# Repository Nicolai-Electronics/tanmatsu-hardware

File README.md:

# Tanmatsu

This repository contains the hardware design files for Tanmatsu, the terminal for hackers.

## Documentation

Need the schematic? [It's in this repository as a PDF file](schematic.pdf).

## License

This hardware design may be used under the terms of the [CERN-OHL-P](LICENSE) license.

All organization names, logos, trademarks and artwork including but not limited to the Nicolai Electronics and Tanmatsu branding are all rights reserved for their respective owners and may not be reproduced on derrivative works.

## Authors

Electronics design by:
 - [Nicolai Electronics](https://nicolaielectronics.nl)
 - [Paul Honig](https://github.com/ranzbak)

Special thanks to:
 - [Jay Visschedijk](https://github.com/JayVisschedijk) (Ergonomic board outline)
 - [Wietse Boonstra](https://github.com/Wietsman) (Component footprints)
 - [Kliment Yanev](https://github.com/kliment) (Review)
 - [Jelle Haandrikman](https://github.com/jhaand) (Review)

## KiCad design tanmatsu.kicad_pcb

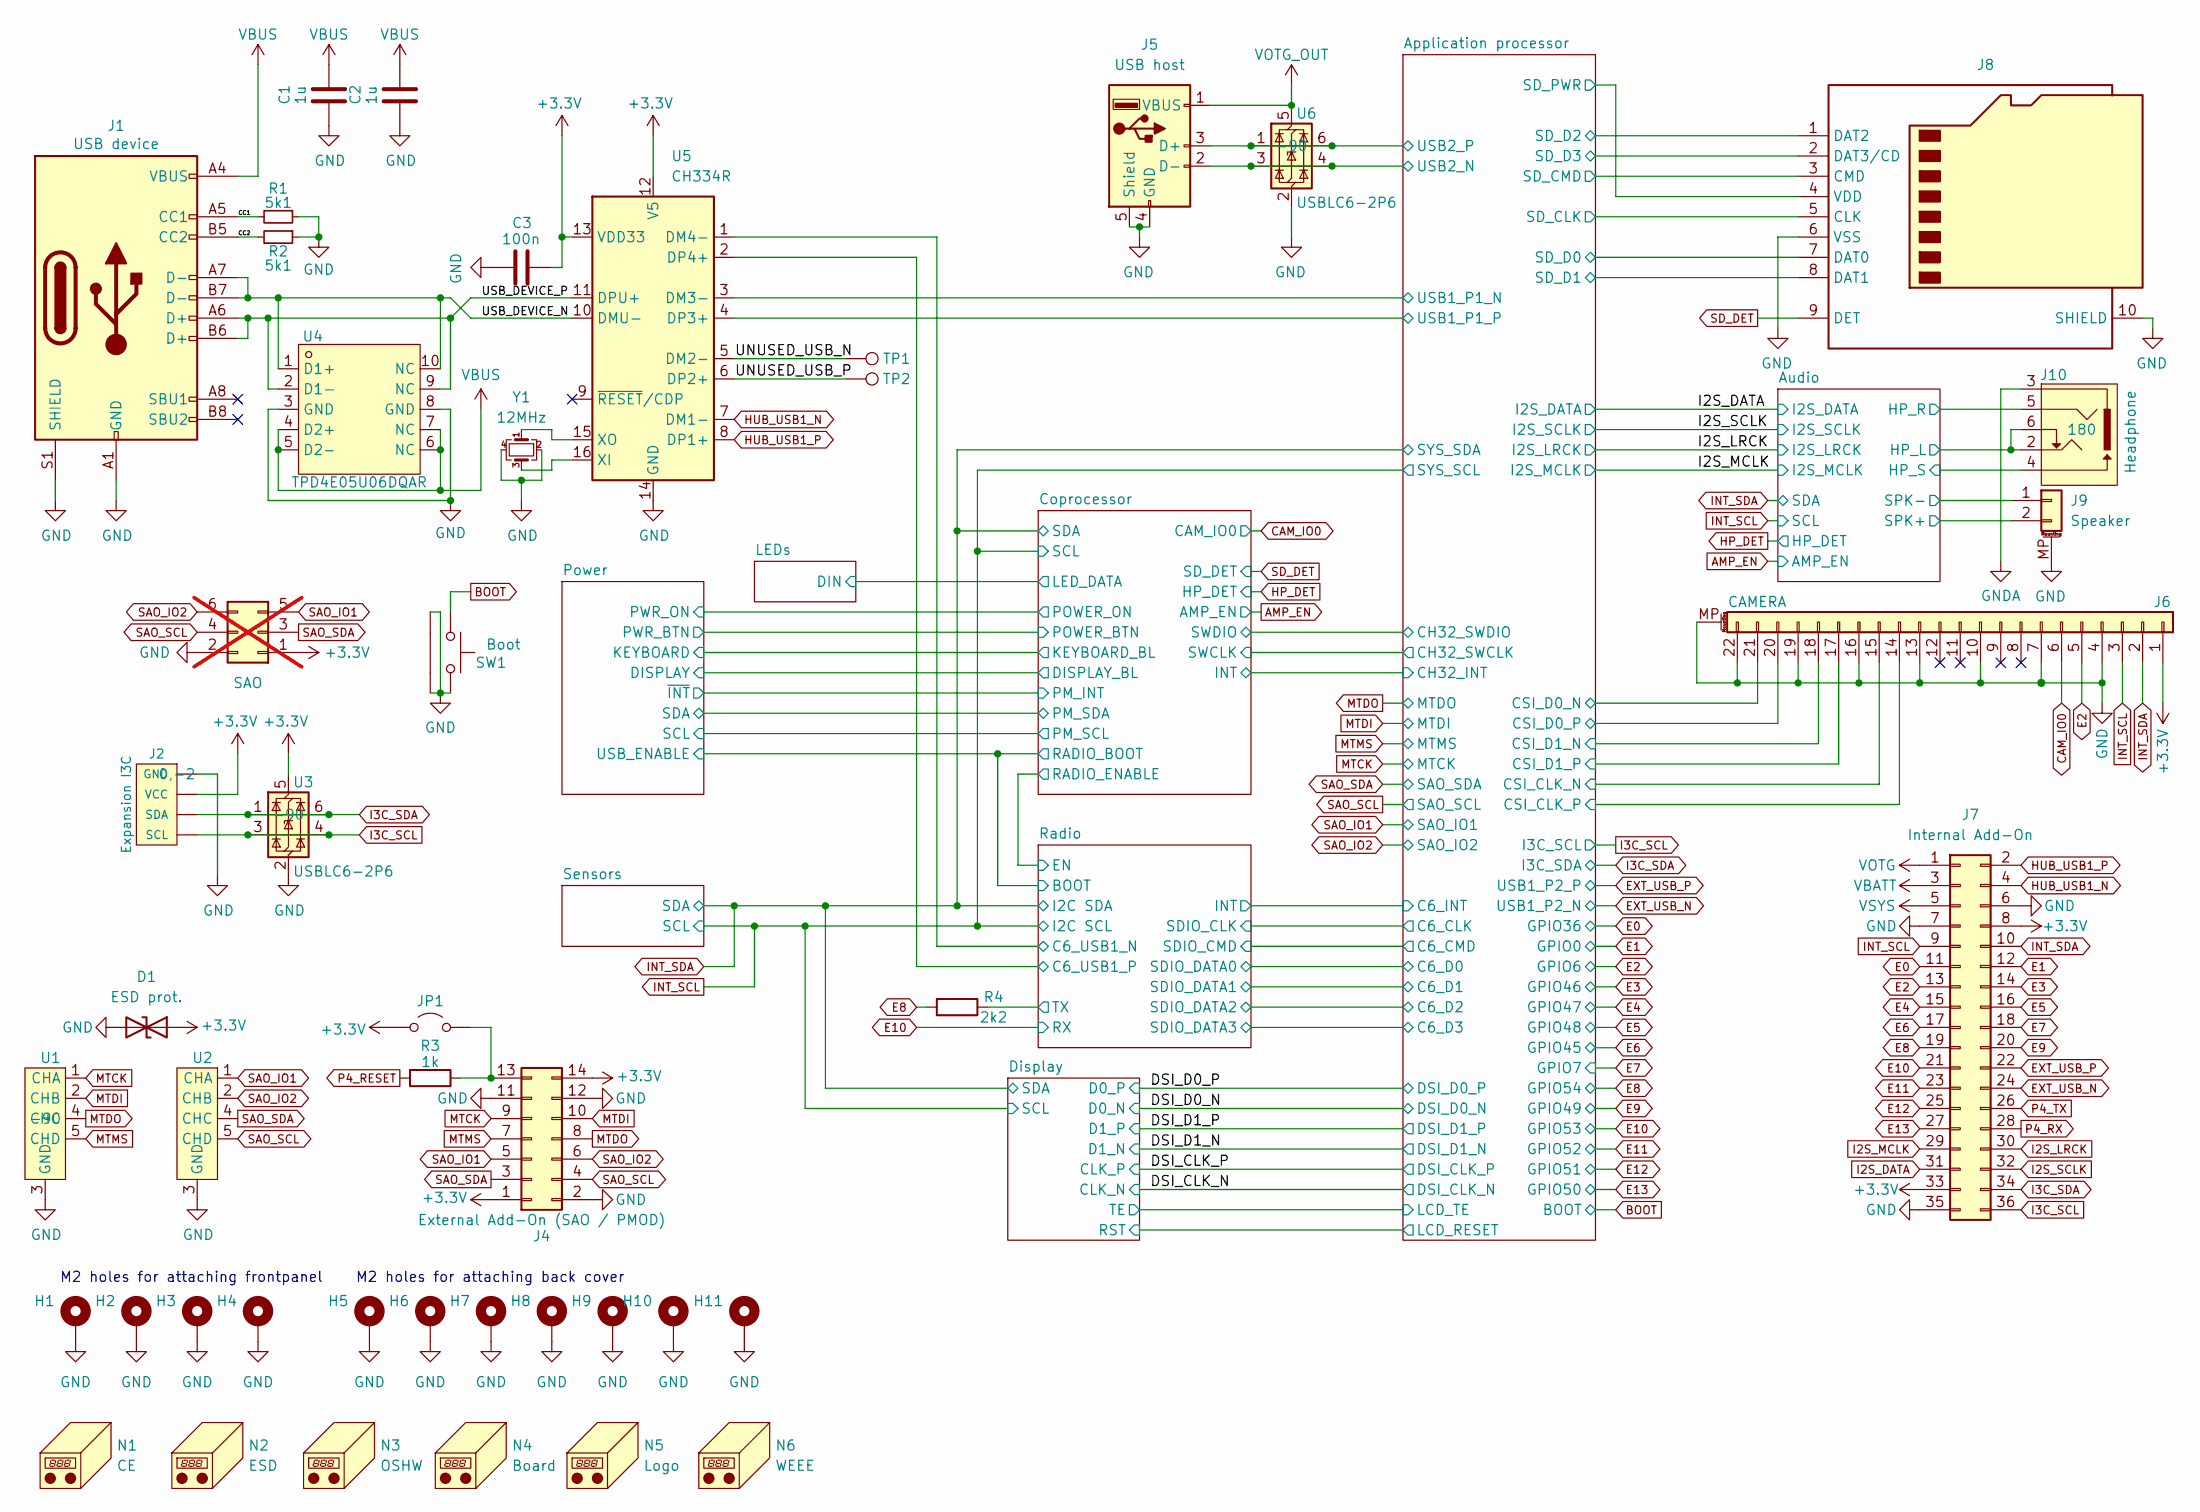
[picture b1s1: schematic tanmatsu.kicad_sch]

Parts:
C1, C2: 1u; C_0603_1608Metric; LCSC C5199872
C3: 100n; C_0402_1005Metric; LCSC C307331
D1: ESD prot.; D_SOD-323; LCSC C22363742
H1, H2, H3, H4, H5, H6, H7, H8, H9, H10, H11: Mounting hole; SMTSO2030CTJ; LCSC C2915626
J1: USB device; USB_C_Receptacle_HRO_TYPE-C-31-M-12; LCSC C165948
J2: Expansion I3C; 1X04_1MM_RA_GND; LCSC C7433425
J3: SAO; PinSocket_2x03_P2.54mm_Vertical_SMD; not fitted
J4: External Add-On (SAO / PMOD); PinSocket_2x07_P2.54mm_Horizontal; LCSC C2936004
J5: USB host; USB-A-TH_JTJ-USB-A-F-10.0-010; LCSC C42576
J6: CAMERA; FPC-SMD_XUNPU_FPC-0.5FX-22PWBH20; LCSC C3446014
J7: Internal Add-On; PinSocket_2x18_P2.54mm_Vertical_SMD; LCSC C3975163
J8: Micro_SD_Card; SD_Card-micro_socket_A; LCSC C7529389
J9: Speaker; Molex_PicoBlade_53261-0271_1x02-1MP_P1.25mm_Horizontal; LCSC C3029359
J10: Headphone; PJ-327ST-SMT; LCSC C319103
JP1: SolderJumper-2_P1.3mm_Open_RoundedPad1.0x1.5mm
N1: CE; CE-Logo_8.5x6mm_SilkScreen
N2: ESD; ESD-Logo_6.6x6mm_SilkScreen
N3: OSHW; OSHW-Logo2_14.6x12mm_SilkScreen
N4: Board; board
N5: Logo; logo_nicolai
N6: WEEE; WEEE-Logo_4.2x6mm_SilkScreen
R1, R2: 5k1; R_0402_1005Metric; LCSC C25905
R3: 1k; R_0402_1005Metric; LCSC C11702
R4: 2k2; R_0402_1005Metric; LCSC C25879
SW1: Boot; KEY-TH_TC-1101V-C-A-W; LCSC C318992
TP1: D-; TestPoint_Pad_D1.0mm
TP2: D+; TestPoint_Pad_D1.0mm
U1, U2: ESD; Diodes_UDFN-10_1.0x2.5mm_P0.5mm; LCSC C5180236
U3, U6: USBLC6-2P6; SOT-666; LCSC C2827693
U4: TPD4E05U06DQAR; USON-10_L2.5-W1.0-P0.50-BL; LCSC C138714
U5: CH334R; QSOP-16_3.9x4.9mm_P0.635mm; LCSC C4154405
Y1: 12MHz; Crystal_SMD_2520-4Pin_2.5x2.0mm; LCSC C284156

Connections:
+3.3V: C3.1, D1.1 (A1), J2.2 (VCC), J3.1, J4.1, J4.14, J6.1, J7.8, J7.33, JP1.1 (A), U3.5 (VBUS), U5.12 (V5), U5.13 (VDD33); also elsewhere on the board
/Application processor/CSI_CLK_N: J6.15; also elsewhere on the board
/Application processor/CSI_CLK_P: J6.14; also elsewhere on the board
/Application processor/CSI_D0_N: J6.21; also elsewhere on the board
/Application processor/CSI_D0_P: J6.20; also elsewhere on the board
/Application processor/CSI_D1_N: J6.18; also elsewhere on the board
/Application processor/CSI_D1_P: J6.17; also elsewhere on the board
/Application processor/SD_CLK: J8.5 (CLK); also elsewhere on the board
/Application processor/SD_CMD: J8.3 (CMD); also elsewhere on the board
/Application processor/SD_D0: J8.7 (DAT0); also elsewhere on the board
/Application processor/SD_D1: J8.8 (DAT1); also elsewhere on the board
/Application processor/SD_D2: J8.1 (DAT2); also elsewhere on the board
/Application processor/SD_D3: J8.2 (DAT3/CD); also elsewhere on the board
/Application processor/SD_PWR: J8.4 (VDD); also elsewhere on the board
/Application processor/USB1_P1_N: U5.3 (DM3-); also elsewhere on the board
/Application processor/USB1_P1_P: U5.4 (DP3+); also elsewhere on the board
/Application processor/USB2_N: J5.2 (D-), U6.3 (I/O2), U6.4 (I/O2); also elsewhere on the board
/Application processor/USB2_P: J5.3 (D+), U6.1 (I/O1), U6.6 (I/O1); also elsewhere on the board
/Audio/HP_L: J10.2, J10.6; also elsewhere on the board
/Audio/HP_R: J10.5; also elsewhere on the board
/Audio/HP_S: J10.4; also elsewhere on the board
/Audio/SPK+: J9.2; also elsewhere on the board
/Audio/SPK-: J9.1; also elsewhere on the board
/CC1: J1.A5 (CC1), R1.2
/CC2: J1.B5 (CC2), R2.2
/Radio/C6_USB1_N: U5.1 (DM4-); also elsewhere on the board
/Radio/C6_USB1_P: U5.2 (DP4+); also elsewhere on the board
/Radio/TX: R4.1; also elsewhere on the board
/UNUSED_USB_N: TP1.1 (1_1), U5.5 (DM2-)
/UNUSED_USB_P: TP2.1 (1_1), U5.6 (DP2+)
/USB_DEVICE_N: J1.A7 (D-), J1.B7 (D-), U4.1 (D1+), U4.10 (NC), U5.10 (DMU-)
/USB_DEVICE_P: J1.A6 (D+), J1.B6 (D+), U4.2 (D1-), U4.9 (NC), U5.11 (DPU+)
BOOT: SW1.1; also elsewhere on the board
CAM_IO0: J6.6; also elsewhere on the board
E0: J7.11; also elsewhere on the board
E1: J7.12; also elsewhere on the board
E2: J6.5, J7.13; also elsewhere on the board
E3: J7.14; also elsewhere on the board
E4: J7.15; also elsewhere on the board
E5: J7.16; also elsewhere on the board
E6: J7.17; also elsewhere on the board
E7: J7.18; also elsewhere on the board
E8: J7.19, R4.2; also elsewhere on the board
E9: J7.20; also elsewhere on the board
E10: J7.21; also elsewhere on the board
E11: J7.23; also elsewhere on the board
E12: J7.25; also elsewhere on the board
E13: J7.27; also elsewhere on the board
EXT_USB_N: J7.24; also elsewhere on the board
EXT_USB_P: J7.22; also elsewhere on the board
GND: C1.2, C2.2, C3.2, D1.2 (A2), H1.1 (1_1), H2.1 (1_1), H3.1 (1_1), H4.1 (1_1), H5.1 (1_1), H6.1 (1_1), H7.1 (1_1), H8.1 (1_1), H9.1 (1_1), H10.1 (1_1), H11.1 (1_1), J1.A1 (GND), J1.A12 (GND), J1.B1 (GND), J1.B12 (GND), J1.S1 (SHIELD), J2.1 (GND), J2.5, J2.6, J3.2, J4.2, J4.11, J4.12, J5.4 (GND), J5.5 (Shield), J6.4, J6.7, J6.10, J6.13, J6.16, J6.19, J6.22, J6.MP (MountPin), J7.6, J7.7, J7.35, J8.6 (VSS), J8.10 (SHIELD), J9.MP (MountPin), R1.1, R2.1, SW1.2, SW1.3, SW1.4, U1.3 (GND), U1.8 (GND), U2.3 (GND), U2.8 (GND), U3.2 (GND), U4.3 (GND), U4.8 (GND), U5.14 (GND), U6.2 (GND), Y1.2, Y1.4; also elsewhere on the board
GNDA: J10.3; also elsewhere on the board
HUB_USB1_N: J7.4, U5.7 (DM1-)
HUB_USB1_P: J7.2, U5.8 (DP1+)
I2S_DATA: J7.31; also elsewhere on the board
I2S_LRCK: J7.30; also elsewhere on the board
I2S_MCLK: J7.29; also elsewhere on the board
I2S_SCLK: J7.32; also elsewhere on the board
I3C_SCL: J2.4 (SCL), J7.36, U3.3 (I/O2), U3.4 (I/O2); also elsewhere on the board
I3C_SDA: J2.3 (SDA), J7.34, U3.1 (I/O1), U3.6 (I/O1); also elsewhere on the board
INT_SCL: J6.3, J7.9; also elsewhere on the board
INT_SDA: J6.2, J7.10; also elsewhere on the board
MTCK: J4.9, U1.1 (CHA), U1.10 (CHA); also elsewhere on the board
MTDI: J4.10, U1.2 (CHB), U1.9 (CHB); also elsewhere on the board
MTDO: J4.8, U1.4 (CHC), U1.7 (CHC); also elsewhere on the board
MTMS: J4.7, U1.5 (CHD), U1.6 (CHD); also elsewhere on the board
unnamed: J4.13, JP1.2 (B), R3.1
unnamed: U5.16 (XI), Y1.3
unnamed: U5.15 (XO), Y1.1
P4_RESET: R3.2; also elsewhere on the board
P4_RX: J7.28; also elsewhere on the board
P4_TX: J7.26; also elsewhere on the board
SAO_IO1: J3.5, J4.5, U2.1 (CHA), U2.10 (CHA); also elsewhere on the board
SAO_IO2: J3.6, J4.6, U2.2 (CHB), U2.9 (CHB); also elsewhere on the board
SAO_SCL: J3.4, J4.4, U2.5 (CHD), U2.6 (CHD); also elsewhere on the board
SAO_SDA: J3.3, J4.3, U2.4 (CHC), U2.7 (CHC); also elsewhere on the board
SD_DET: J8.9 (DET); also elsewhere on the board
VBATT: J7.3; also elsewhere on the board
VBUS: C1.1, C2.1, J1.A4 (VBUS), J1.A9 (VBUS), J1.B4 (VBUS), J1.B9 (VBUS), U4.4 (D2+), U4.5 (D2-), U4.6 (NC), U4.7 (NC); also elsewhere on the board
VOTG: J7.1; also elsewhere on the board
VOTG_OUT: J5.1 (VBUS), U6.5 (VBUS); also elsewhere on the board
VSYS: J7.5; also elsewhere on the board

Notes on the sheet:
M2 holes for attaching back cover
M2 holes for attaching frontpanel

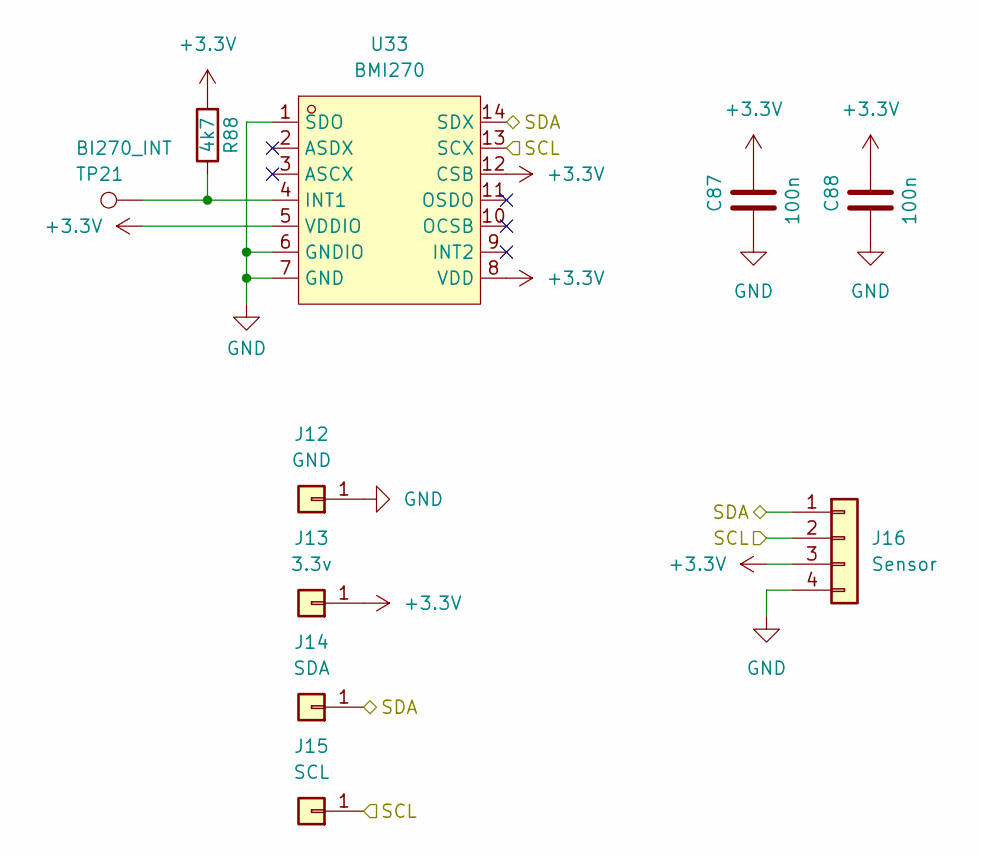
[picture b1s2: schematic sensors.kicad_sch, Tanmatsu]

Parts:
C87, C88: 100n; C_0402_1005Metric; LCSC C307331
J12: GND; Harwin S7091-42R
J13: 3.3v; Harwin S7091-42R
J14: SDA; Harwin S7091-42R
J15: SCL; Harwin S7091-42R
J16: Sensor; PinHeader_1x04_P2.54mm_Vertical; LCSC C2691448
R88: 4k7; R_0402_1005Metric; LCSC C25900
TP21: BI270_INT; TestPoint_Pad_D1.0mm
U33: BMI270; LGA-14_L3.0-W2.5-P0.50-BR; LCSC C2836813

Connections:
+3.3V: C87.1, C88.1, J13.1 (Pin_1_1), J16.3, R88.2, U33.5 (VDDIO), U33.8 (VDD), U33.12 (CSB); also elsewhere on the board
GND: C87.2, C88.2, J12.1 (Pin_1_1), J16.4, U33.1 (SDO), U33.6 (GNDIO), U33.7 (GND); also elsewhere on the board
INT_SCL: J15.1 (Pin_1_1), J16.2, U33.13 (SCX); also elsewhere on the board
INT_SDA: J14.1 (Pin_1_1), J16.1, U33.14 (SDX); also elsewhere on the board
unnamed: R88.1, TP21.1 (1_1), U33.4 (INT1)

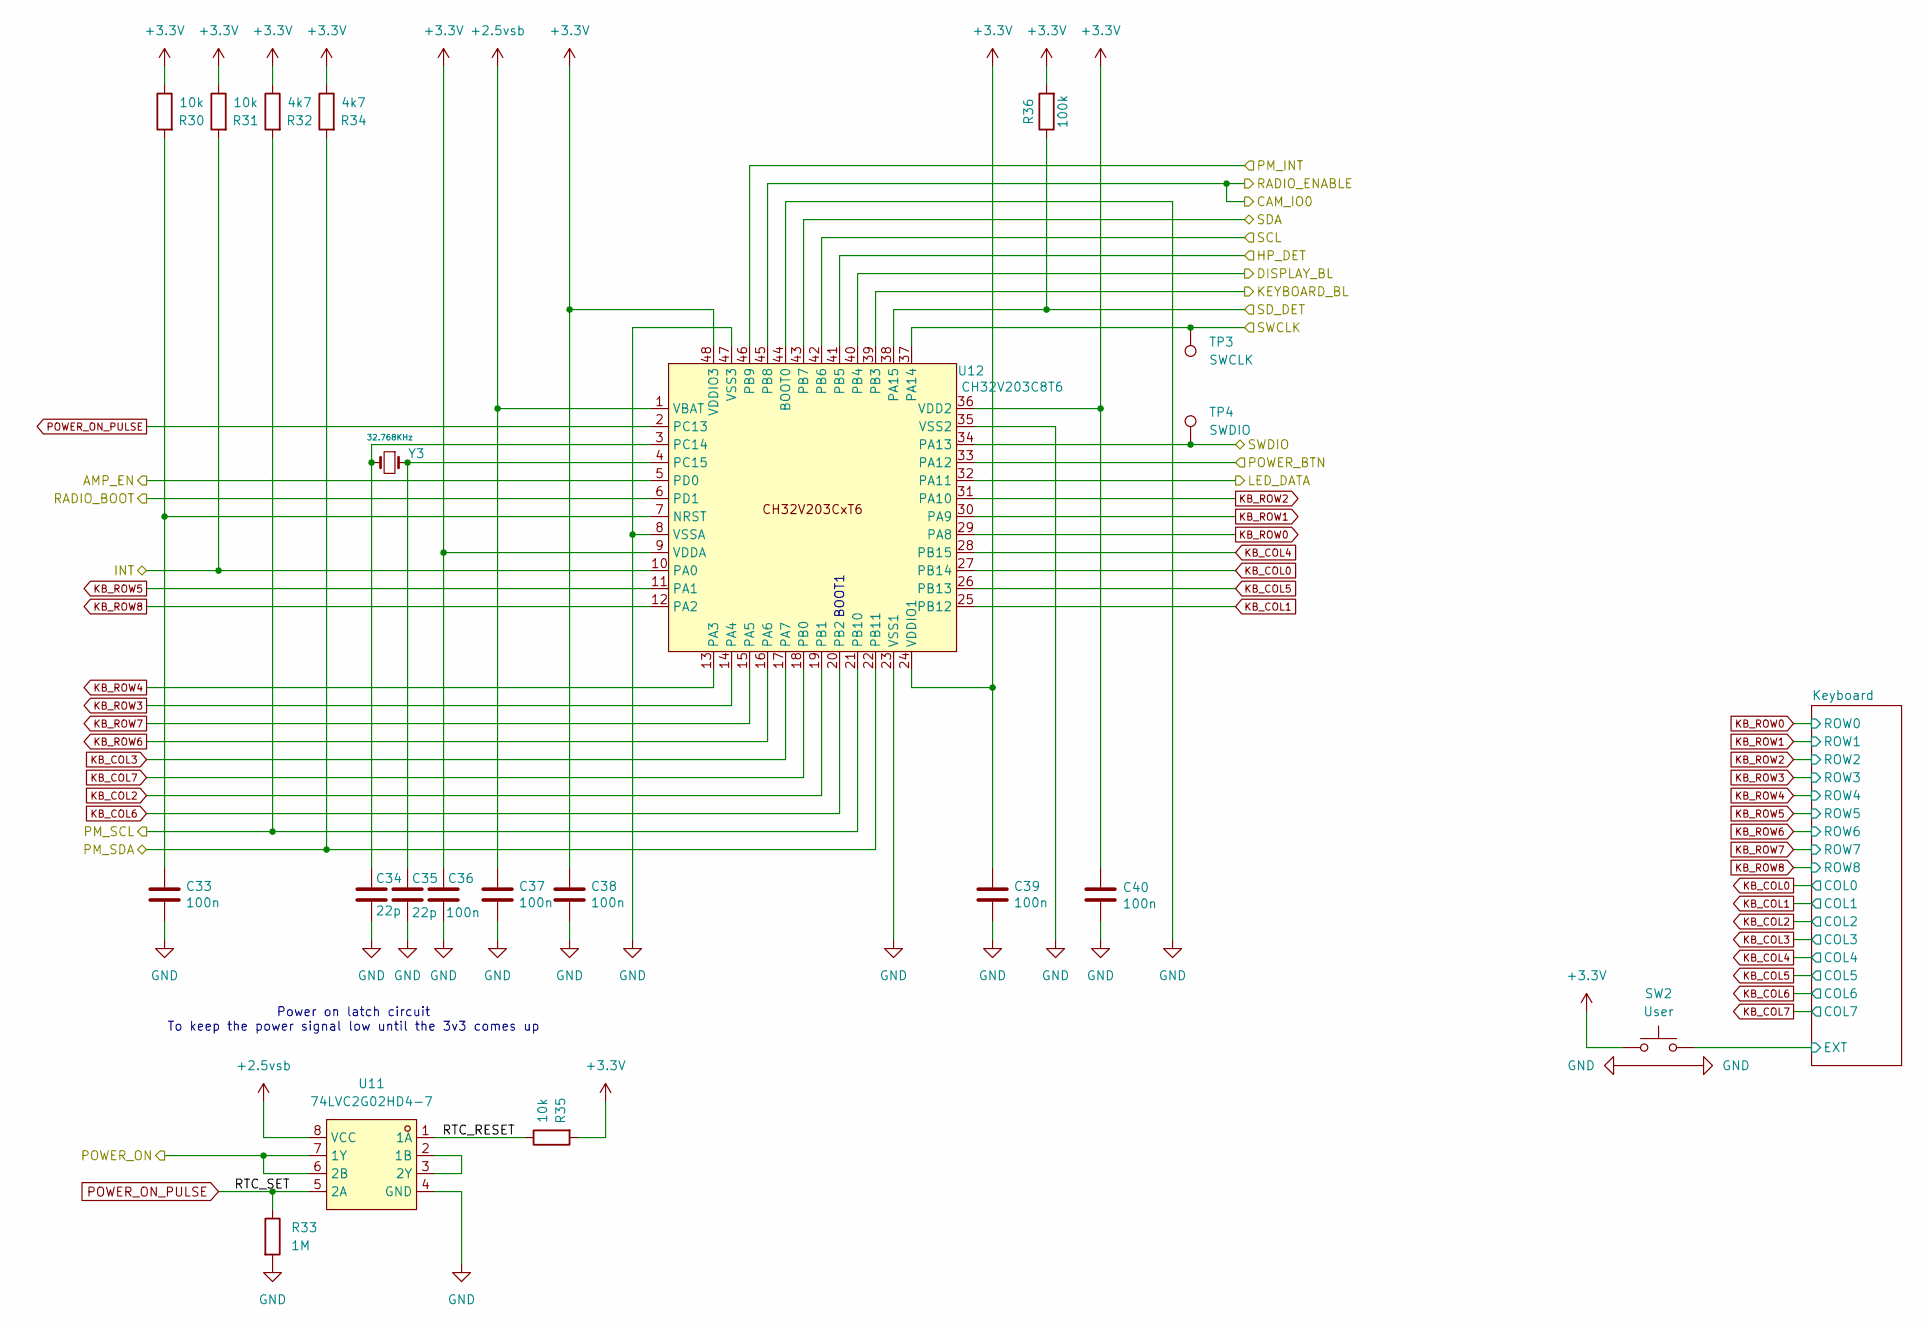
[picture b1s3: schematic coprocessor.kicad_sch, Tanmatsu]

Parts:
C33, C36, C37, C38, C39, C40: 100n; C_0402_1005Metric; LCSC C307331
C34, C35: 22p; C_0402_1005Metric; LCSC C1555
R30, R31, R35: 10k; R_0402_1005Metric; LCSC C60490
R32, R34: 4k7; R_0402_1005Metric; LCSC C25900
R33: 1M; R_0402_1005Metric; LCSC C26083
R36: 100k; R_0402_1005Metric; LCSC C25741
SW2: User; KEY-TH_TC-1101V-C-A-W; LCSC C318992
TP3: SWCLK; TestPoint_Pad_1.0x1.0mm
TP4: SWDIO; TestPoint_Pad_1.0x1.0mm
U11: 74LVC2G02HD4-7; X2-DFN2010-8_L2.0-W1.0-P0.50-BL; LCSC C842640
U12: CH32V203C8T6; LQFP-48_7x7mm_P0.5mm; LCSC C3001172
Y3: 32.768KHz; Crystal_SMD_3215-2Pin_3.2x1.5mm; LCSC C95361

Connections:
+2.5vsb: C37.1, U11.8 (VCC), U12.1 (VBAT); also elsewhere on the board
+3.3V: C36.1, C38.1, C39.1, C40.1, R30.1, R31.1, R32.1, R34.1, R35.2, R36.2, SW2.1, U12.9 (VDDA), U12.24 (VDDIO1), U12.36 (VDD2), U12.48 (VDDIO3); also elsewhere on the board
/Application processor/CH32_INT: R31.2, U12.10 (PA0); also elsewhere on the board
/Application processor/CH32_SWCLK: TP3.1 (1_1), U12.37 (PA14); also elsewhere on the board
/Application processor/CH32_SWDIO: TP4.1 (1_1), U12.34 (PA13); also elsewhere on the board
/Coprocessor/DISPLAY_BL: U12.40 (PB4); also elsewhere on the board
/Coprocessor/KEYBOARD_BL: U12.39 (PB3); also elsewhere on the board
/Coprocessor/Keyboard/EXT: SW2.2; also elsewhere on the board
/Coprocessor/LED_DATA: U12.32 (PA11); also elsewhere on the board
/Coprocessor/PM_INT: U12.46 (PB9); also elsewhere on the board
/Coprocessor/PM_SCL: R32.2, U12.21 (PB10); also elsewhere on the board
/Coprocessor/PM_SDA: R34.2, U12.22 (PB11); also elsewhere on the board
/Coprocessor/POWER_BTN: U12.33 (PA12); also elsewhere on the board
/Coprocessor/POWER_ON: U11.6 (2B), U11.7 (1Y); also elsewhere on the board
/Coprocessor/RADIO_BOOT: U12.6 (PD1); also elsewhere on the board
/Coprocessor/RTC_RESET: R35.1, U11.1 (1A)
AMP_EN: U12.5 (PD0); also elsewhere on the board
CAM_IO0: U12.45 (PB8); also elsewhere on the board
GND: C33.2, C34.2, C35.2, C36.2, C37.2, C38.2, C39.2, C40.2, R33.2, SW2.3, SW2.4, U11.4 (GND), U12.8 (VSSA), U12.23 (VSS1), U12.35 (VSS2), U12.44 (BOOT0), U12.47 (VSS3); also elsewhere on the board
HP_DET: U12.41 (PB5); also elsewhere on the board
INT_SCL: U12.42 (PB6); also elsewhere on the board
INT_SDA: U12.43 (PB7); also elsewhere on the board
KB_COL0: U12.27 (PB14); also elsewhere on the board
KB_COL1: U12.25 (PB12); also elsewhere on the board
KB_COL2: U12.19 (PB1); also elsewhere on the board
KB_COL3: U12.17 (PA7); also elsewhere on the board
KB_COL4: U12.28 (PB15); also elsewhere on the board
KB_COL5: U12.26 (PB13); also elsewhere on the board
KB_COL6: U12.20 (PB2); also elsewhere on the board
KB_COL7: U12.18 (PB0); also elsewhere on the board
KB_ROW0: U12.29 (PA8); also elsewhere on the board
KB_ROW1: U12.30 (PA9); also elsewhere on the board
KB_ROW2: U12.31 (PA10); also elsewhere on the board
KB_ROW3: U12.14 (PA4); also elsewhere on the board
KB_ROW4: U12.13 (PA3); also elsewhere on the board
KB_ROW5: U12.11 (PA1); also elsewhere on the board
KB_ROW6: U12.16 (PA6); also elsewhere on the board
KB_ROW7: U12.15 (PA5); also elsewhere on the board
KB_ROW8: U12.12 (PA2); also elsewhere on the board
unnamed: U11.2 (1B), U11.3 (2Y)
unnamed: C33.1, R30.2, U12.7 (NRST)
unnamed: C34.1, U12.3 (PC14), Y3.2
unnamed: C35.1, U12.4 (PC15), Y3.1
POWER_ON_PULSE: R33.1, U11.5 (2A), U12.2 (PC13)
SD_DET: R36.1, U12.38 (PA15); also elsewhere on the board

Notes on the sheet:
Power on latch circuit To keep the power signal low until the 3v3 comes up
BOOT1

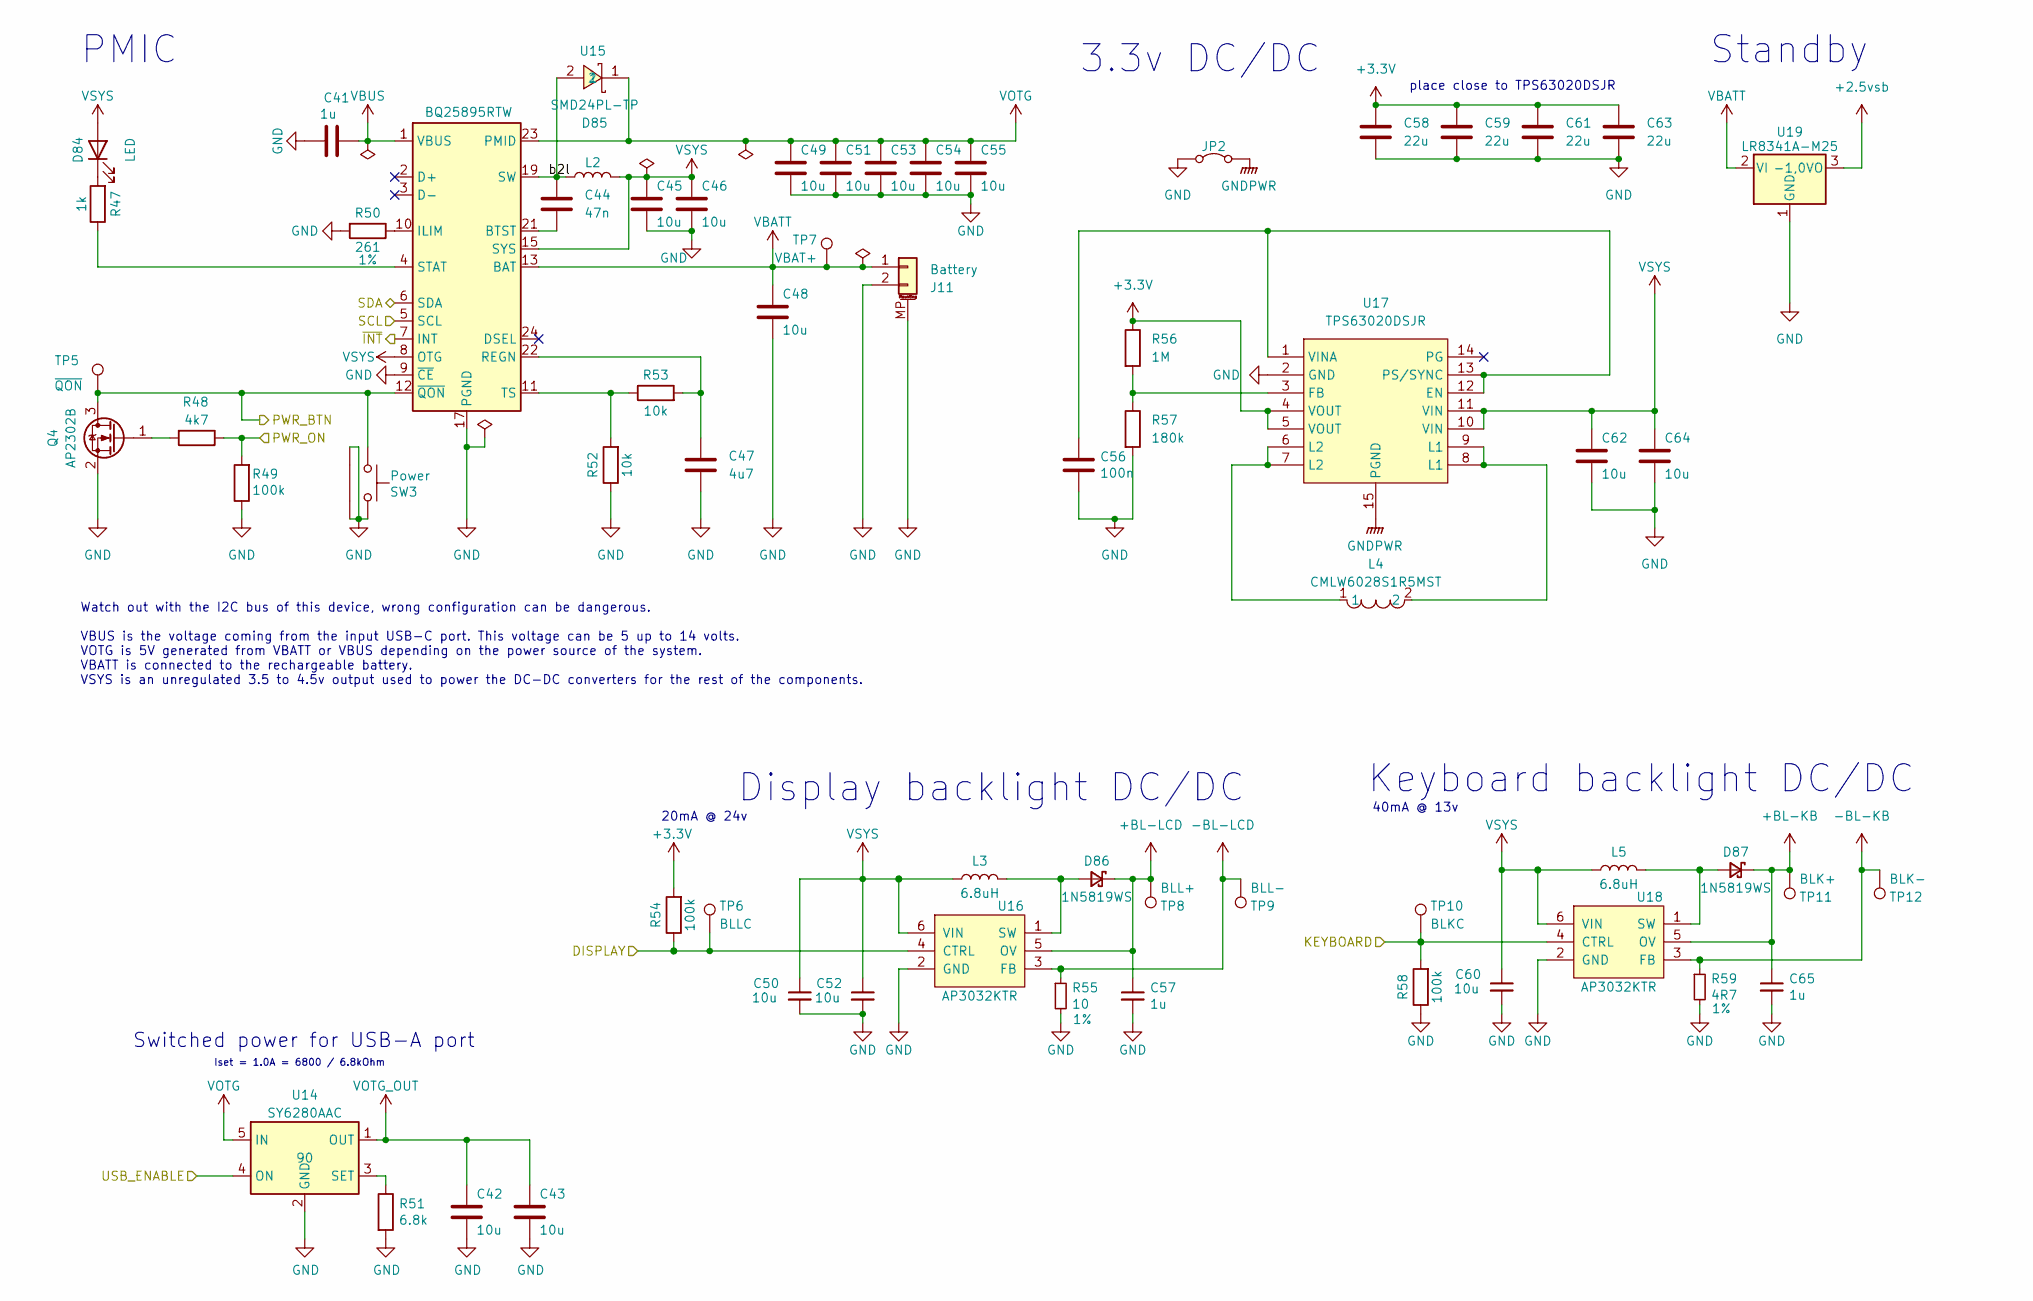
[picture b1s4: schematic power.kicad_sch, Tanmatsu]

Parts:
C41, C57, C65: 1u; C_0603_1608Metric; LCSC C5199872
C42, C43, C45, C46, C48, C49, C50, C51, C52, C53, C54, C55, C60, C62, C64: 10u; C_0805_2012Metric; LCSC C3039694
C44: 47n; C_0603_1608Metric; LCSC C469624
C47: 4u7; C_0603_1608Metric; LCSC C69335
C56: 100n; C_0402_1005Metric; LCSC C307331
C58, C59, C61, C63: 22u; C_0805_2012Metric; LCSC C602037
D84: LED; LED_0603_1608Metric; LCSC C7496820
D85: SMD24PL-TP; SOD-123_L2.8-W1.8-LS3.7-RD; LCSC C151787
D86, D87: 1N5819WS; D_SOD-323; LCSC C369937
J11: Battery; CONN-SMD_PH-2AWB; LCSC C20598817
JP2: NetTie-2_SMD_Pad0.5mm
L2: YHNR4020-2R2M; L_Wurth_WE-LQSH-4020; LCSC C2926400
L3, L5: 6.8uH; IND-SMD_L4.0-W4.0; LCSC C520306
L4: CMLW6028S1R5MST; IND-SMD_L6.0-W6.0; LCSC C431354
Q4: AP2302B; SOT-23; LCSC C406812
R47: 1k; R_0402_1005Metric; LCSC C11702
R48: 4k7; R_0402_1005Metric; LCSC C25900
R49, R54, R58: 100k; R_0402_1005Metric; LCSC C25741
R50: 261; R_0402_1005Metric; LCSC C7467416
R51: 6.8k; R_0402_1005Metric; LCSC C25917
R52, R53: 10k; R_0402_1005Metric; LCSC C60490
R55: 10; R_0402_1005Metric; LCSC C25077
R56: 1M; R_0402_1005Metric_Pad0.72x0.64mm_HandSolder; LCSC C26083
R57: 180k; R_0402_1005Metric_Pad0.72x0.64mm_HandSolder; LCSC C2909325
R59: 4R7; R_0402_1005Metric; LCSC C25121
SW3: Power; KEY-TH_TC-1101V-C-A-W; LCSC C318992
TP5: ~{QON}; TestPoint_Pad_D1.0mm
TP6: BLLC; TestPoint_Pad_D1.0mm
TP7: VBAT+; TestPoint_Pad_D1.0mm
TP8: BLL+; TestPoint_Pad_D1.0mm
TP9: BLL-; TestPoint_Pad_D1.0mm
TP10: BLKC; TestPoint_Pad_D1.0mm
TP11: BLK+; TestPoint_Pad_D1.0mm
TP12: BLK-; TestPoint_Pad_D1.0mm
U14: SY6280AAC; SOT-23-5; LCSC C55136
U15: BQ25895RTW; Texas_S-PWQFN-N24_EP2.7x2.7mm_ThermalVias; LCSC C80200
U16, U18: AP3032KTR; SOT-23-6; LCSC C264086
U17: TPS63020DSJR; VSON-14_L4.0-W3.0-P0.50-BL-EP_TI_DSJ; LCSC C15483
U19: LR8341A-M25; SOT-89-3; LCSC C5205210

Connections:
+2.5vsb: U19.3 (VO); also elsewhere on the board
+3.3V: C58.1, C59.1, C61.1, C63.1, R54.2, R56.1, U17.4 (VOUT), U17.5 (VOUT); also elsewhere on the board
+BL-KB: C65.1, D87.1 (K), TP11.1 (1_1), U18.5 (OV); also elsewhere on the board
+BL-LCD: C57.1, D86.1 (K), TP8.1 (1_1), U16.5 (OV); also elsewhere on the board
-BL-KB: R59.1, TP12.1 (1_1), U18.3 (FB); also elsewhere on the board
-BL-LCD: R55.1, TP9.1 (1_1), U16.3 (FB); also elsewhere on the board
/Coprocessor/DISPLAY_BL: R54.1, TP6.1 (1_1), U16.4 (CTRL); also elsewhere on the board
/Coprocessor/KEYBOARD_BL: R58.2, TP10.1 (1_1), U18.4 (CTRL); also elsewhere on the board
/Coprocessor/PM_INT: U15.7 (INT); also elsewhere on the board
/Coprocessor/PM_SCL: U15.5 (SCL); also elsewhere on the board
/Coprocessor/PM_SDA: U15.6 (SDA); also elsewhere on the board
/Coprocessor/POWER_BTN: Q4.3 (D), SW3.1, TP5.1 (1_1), U15.12 (~QON); also elsewhere on the board
/Coprocessor/POWER_ON: R48.1, R49.2; also elsewhere on the board
/Coprocessor/RADIO_BOOT: U14.4 (ON); also elsewhere on the board
/Power/b2l: C44.1, D85.2, L2.1, U15.19 (SW), U15.20 (SW)
GND: C41.2, C42.2, C43.2, C45.2, C46.2, C47.2, C48.2, C49.2, C50.2, C51.2, C52.2, C53.2, C54.2, C55.2, C56.2, C57.2, C58.2, C59.2, C60.2, C61.2, C62.2, C63.2, C64.2, C65.2, J11.2, J11.MP (MountPin), JP2.1 (A), Q4.2 (S), R49.1, R50.2, R51.2, R52.1, R55.2, R57.2, R58.1, R59.2, SW3.2, SW3.3, SW3.4, U14.2 (GND), U15.9 (~CE), U15.17 (PGND), U15.18 (PGND), U15.25 (PGND), U16.2 (GND), U17.2 (GND), U18.2 (GND), U19.1 (GND); also elsewhere on the board
GNDPWR: JP2.2 (B), U17.15 (PGND)
unnamed: D84.1 (K), R47.2
unnamed: D86.2 (A), L3.2, U16.1 (SW)
unnamed: D87.2 (A), L5.2, U18.1 (SW)
unnamed: L4.1, U17.6 (L2), U17.7 (L2)
unnamed: L4.2, U17.8 (L1), U17.9 (L1)
unnamed: Q4.1 (G), R48.2
unnamed: R51.1, U14.3 (SET)
unnamed: C44.2, U15.21 (BTST)
unnamed: R50.1, U15.10 (ILIM)
unnamed: C47.1, R53.2, U15.22 (REGN)
unnamed: R47.1, U15.4 (STAT)
unnamed: R52.2, R53.1, U15.11 (TS)
unnamed: C56.1, U17.1 (VINA), U17.12 (EN), U17.13 (PS/SYNC)
unnamed: R56.2, R57.1, U17.3 (FB)
VBATT: C48.1, J11.1, TP7.1 (1_1), U15.13 (BAT), U15.14 (BAT), U19.2 (VI); also elsewhere on the board
VBUS: C41.1, U15.1 (VBUS); also elsewhere on the board
VOTG: C49.1, C51.1, C53.1, C54.1, C55.1, D85.1, U14.5 (IN), U15.23 (PMID); also elsewhere on the board
VOTG_OUT: C42.1, C43.1, U14.1 (OUT); also elsewhere on the board
VSYS: C45.1, C46.1, C50.1, C52.1, C60.1, C62.1, C64.1, D84.2 (A), L2.2, L3.1, L5.1, U15.8 (OTG), U15.15 (SYS), U15.16 (SYS), U16.6 (VIN), U17.10 (VIN), U17.11 (VIN), U18.6 (VIN); also elsewhere on the board

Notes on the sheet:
Switched power for USB-A port
Iset = 1.0A = 6800 / 6.8kOhm
place close to TPS63020DSJR
Standby
3.3v DC/DC
20mA @ 24v
PMIC
Display backlight DC/DC
Keyboard backlight DC/DC
40mA @ 13v
Watch out with the I2C bus of this device, wrong configuration can be dangerous. VBUS is the voltage coming from the input USB-C port. This voltage can be 5 up to 14 volts. VOTG is 5V generated from VBATT or VBUS depending on the power source of the system. VBATT is connected to the rechargeable ba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

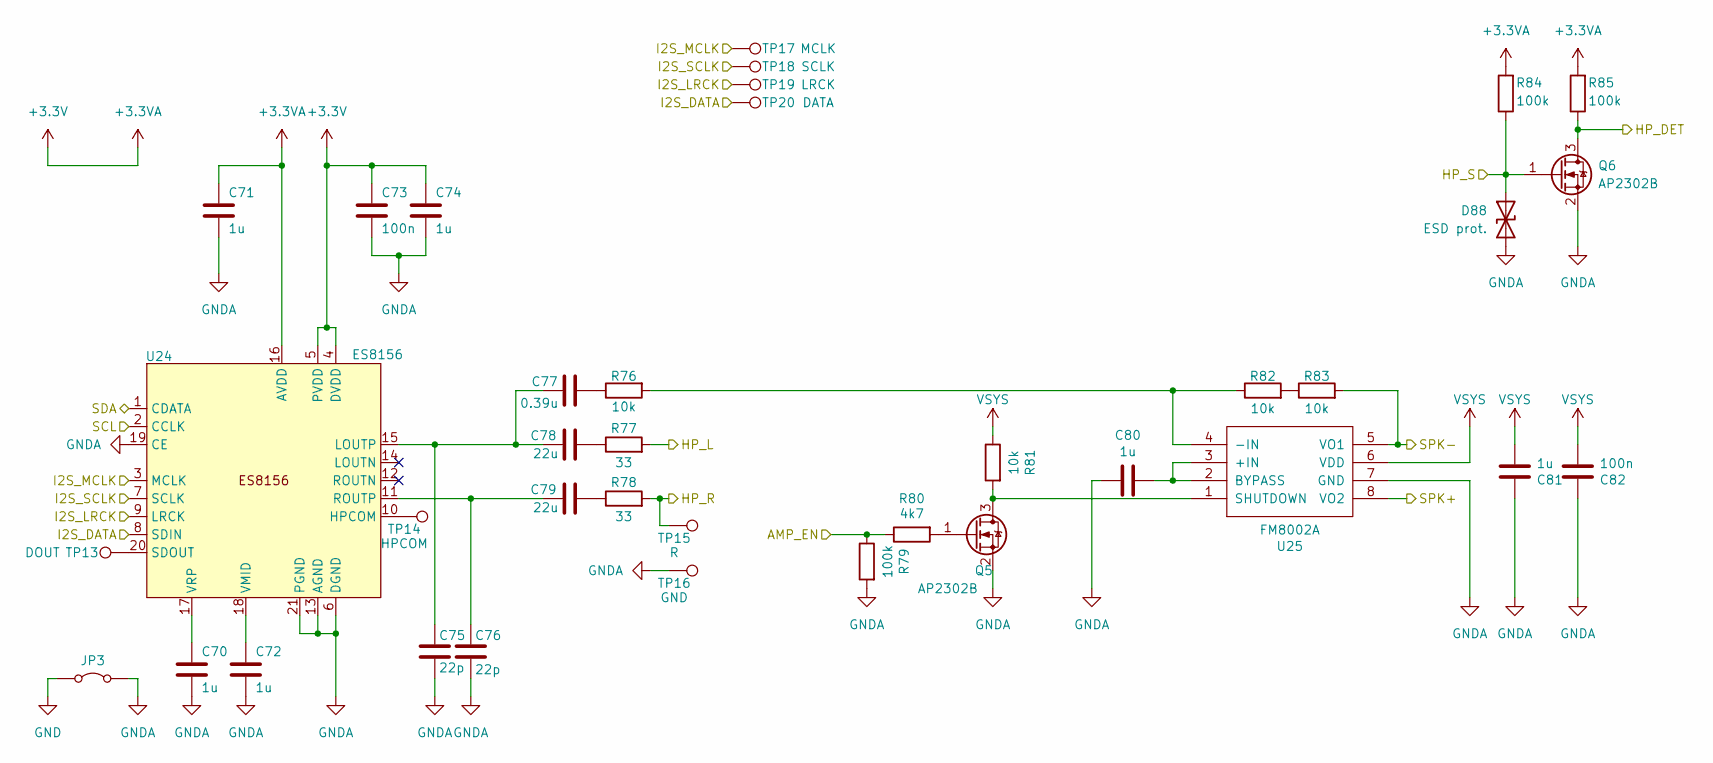
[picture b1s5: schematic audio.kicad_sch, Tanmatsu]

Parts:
C70, C71, C72, C74, C80, C81: 1u; C_0603_1608Metric; LCSC C5199872
C73, C82: 100n; C_0402_1005Metric; LCSC C307331
C75, C76: 22p; C_0402_1005Metric; LCSC C1555
C77: 0.39u; C_0603_1608Metric; LCSC C1623
C78, C79: 22u; C_0805_2012Metric; LCSC C602037
D88: ESD prot.; D_SOD-323; LCSC C22363742
JP3: NetTie-2_SMD_Pad0.5mm
Q5, Q6: AP2302B; SOT-23; LCSC C406812
R76, R81, R82, R83: 10k; R_0402_1005Metric; LCSC C60490
R77, R78: 33; R_0402_1005Metric; LCSC C25105
R79, R84, R85: 100k; R_0402_1005Metric; LCSC C25741
R80: 4k7; R_0402_1005Metric; LCSC C25900
TP13: DOUT; TestPoint_Pad_1.0x1.0mm
TP14: HPCOM; TestPoint_Pad_1.0x1.0mm
TP15: R; TestPoint_Pad_1.0x1.0mm
TP16: GND; TestPoint_Pad_1.0x1.0mm
TP17: MCLK; TestPoint_Pad_1.0x1.0mm
TP18: SCLK; TestPoint_Pad_1.0x1.0mm
TP19: LRCK; TestPoint_Pad_1.0x1.0mm
TP20: DATA; TestPoint_Pad_1.0x1.0mm
U24: ES8156; VQFN-20-1EP_3x3mm_P0.4mm_EP1.7x1.7mm; LCSC C2887138
U25: FM8002A; SSOP-8_3.9x5.05mm_P1.27mm; LCSC C94625

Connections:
+3.3V: C71.1, C73.1, C74.1, R84.2, R85.2, U24.4 (DVDD), U24.5 (PVDD), U24.16 (AVDD); also elsewhere on the board
/Audio/HP_L: R77.2; also elsewhere on the board
/Audio/HP_R: R78.2, TP15.1 (1_1); also elsewhere on the board
/Audio/HP_S: D88.1 (A1), Q6.1 (G), R84.1; also elsewhere on the board
/Audio/SPK+: U25.8 (VO2); also elsewhere on the board
/Audio/SPK-: R83.2, U25.5 (VO1); also elsewhere on the board
AMP_EN: R79.1, R80.1; also elsewhere on the board
GND: JP3.1 (A); also elsewhere on the board
GNDA: C70.2, C71.2, C72.2, C73.2, C74.2, C75.2, C76.2, C80.1, C81.2, C82.2, D88.2 (A2), JP3.2 (B), Q5.2 (S), Q6.2 (S), R79.2, TP16.1 (1_1), U24.6 (DGND), U24.13 (AGND), U24.19 (CE), U24.21 (PGND), U25.7 (GND); also elsewhere on the board
HP_DET: Q6.3 (D), R85.1; also elsewhere on the board
I2S_DATA: TP20.1 (1_1), U24.8 (SDIN); also elsewhere on the board
I2S_LRCK: TP19.1 (1_1), U24.9 (LRCK); also elsewhere on the board
I2S_MCLK: TP17.1 (1_1), U24.3 (MCLK); also elsewhere on the board
I2S_SCLK: TP18.1 (1_1), U24.7 (SCLK); also elsewhere on the board
INT_SCL: U24.2 (CCLK); also elsewhere on the board
INT_SDA: U24.1 (CDATA); also elsewhere on the board
unnamed: C77.1, R76.1
unnamed: C78.2, R77.1
unnamed: C79.2, R78.1
unnamed: Q5.3 (D), R81.2, U25.1 (SHUTDOWN)
unnamed: Q5.1 (G), R80.2
unnamed: R82.2, R83.1
unnamed: TP14.1 (1_1), U24.10 (HPCOM)
unnamed: C75.1, C77.2, C78.1, U24.15 (LOUTP)
unnamed: C76.1, C79.1, U24.11 (ROUTP)
unnamed: TP13.1 (1_1), U24.20 (SDOUT)
unnamed: C72.1, U24.18 (VMID)
unnamed: C70.1, U24.17 (VRP)
unnamed: C80.2, U25.2 (BYPASS), U25.3 (+IN)
unnamed: R76.2, R82.1, U25.4 (-IN)
VSYS: C81.1, C82.1, R81.1, U25.6 (VDD); also elsewhere on the board

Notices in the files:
audio.kicad_sch:
Copyright 2026 Paul Honig
Copyright 2026 Nicolai Electronics
License: CERN-OHL-P
